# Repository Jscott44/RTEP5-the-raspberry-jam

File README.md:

<!-- display the social media buttons in your README -->

<!-- To Link your profile to the media buttons -->

# **The Raspberry Jam**

The realtime Raspberry PI powered digital guitar effects pedal.

<div style="float:left;margin:0 1px 1px 0" markdown="2">

</div>

# **Usage**

Ensure the Raspberry Pi is updated:

```bash
# Update package lists
sudo apt update

# Upgrade installed packages
sudo apt upgrade

# Remove unused packages
sudo apt autoremove

# Clean up package cache
sudo apt clean
```
Install Git 
```bash
# Install Git
sudo apt-get install git -y

# Verify Git installation
git --version
```
Install ALSA resources
```bash
# Install ALSA utilities and libraries
sudo apt-get install alsa-utils libasound2-dev -y

# Verify ALSA installation
aplay --version
```
Install CMake in order to build the project
```bash
# Install CMake
sudo apt-get install cmake -y

# Verify CMake installation
cmake --version
```
Clone the repository
```bash
# Clone the repository from GitHub
git clone https://github.com/Jscott44/RTEP5-the-raspberry-jam.git

# Change directory to the cloned repository
cd RTEP5-the-raspberry-jam

# List files in the repository
ls
```
For use with a generic sound card a device tree overlay needs to be created.

To make sound card master and Raspberry Pi on I2S bus (credit: https://github.com/AkiyukiOkayasu/RaspberryPi_I2S_Slave):
```bash
# Change to device tree directory
cd deviceTree

# Compile on Raspberry Pi  
dtc -@ -H epapr -O dtb -o genericstereoaudiocodec.dtbo -Wno-unit_address_vs_reg genericstereoaudiocodec.dts

# Copy i2smaster.dtbo to /boot/overlays  
sudo cp genericstereoaudiocodec.dtbo /boot/overlays

# Return to repository directory
cd ..
```

Edit /boot/config.txt   
```/boot/config.txt    # Uncomment some or all of these to enable the optional hardware interface
#dtparam=i2c_arm=on
dtparam=i2s=on
#dtparam=spi=on
dtoverlay=genericstereoaudiocodec
```
To make sound card slave and Raspberry Pi master on I2S bus (credit: https://github.com/AkiyukiOkayasu/RaspberryPi_I2S_Master):

```bash
# Compile on Raspberry Pi
# Change to device tree directory
cd deviceTree

dtc -@ -H epapr -O dtb -o i2smaster.dtbo -Wno-unit_address_vs_reg i2smaster.dts

# Copy i2smaster.dtbo to /boot/overlays  
sudo cp i2smaster.dtbo /boot/overlays

# Return to repository directory
cd ..
```

Edit /boot/config.txt  
```/boot/config.txt
# Uncomment some or all of these to enable the optional hardware interface
#dtparam=i2c_arm=on
dtparam=i2s=on
#dtparam=spi=on
dtoverlay=i2smaster
```

Bulding the project with CMake
```bash 
# Create a build directory (optional)
mkdir -p build
cd build

# Configure the build using CMake
cmake ..

# Build the project
make
```
# **Key Features**
- Realtime audio loop
- Cutsomisable effects
- User profiles
- Low cost
- Simple effect creation
- Specialised audio electronics design

# **Social Media Links**
[)][2]
[)][5]

[2]: https://www.instagram.com/the_raspberry_jam/ 
[5]: https://github.com/Jscott44/RTEP5-the-raspberry-jam

# **Authors and Roles**
- **Jed Scott**
  - Project Manager, Software (audio driver), Hardware Lead, Social Media Lead
- **Dario Petinella**
  - Software Lead (audio driver, effects manager), Integration Lead, Hardware (audio)
- **Alan Hamilton**
  - Software (GUI Lead and effects integration), Mechanical Support
- **Elad Perets**
  - Software (effects), Hardware (pedal)
- **Matthew Stewart**
  - Software (GUI)

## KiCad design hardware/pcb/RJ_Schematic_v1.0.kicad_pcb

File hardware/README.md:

# **Hardware**
The Raspberry Jam includes a specialised audio sound card for the capture and playback of high fidelity audio. The impact of the hardware is designed to be as inaudible as possible and all of the effects are achieved digitally in software. The hardware design is modular in nature allowing the cutsomisation to suit different applications.

# **Features**
- Highly integrated stereo audio CODEC
- Sample rates: 44.1kHz, 48kHz, 96kHz or 192kHz
- Hardware or Software control
- On-board oscillator
- 1x mono audio input (guitar)
- 2x stereo outputs (speakers)
- 1x stereo output (headphones with volume control)

# **Audio Inputs and Outputs**
The current version of the sound card supports one single ended mono instrument input up to 2Vrms. 

The output support two single ended connectors to create a stereo speaker output with a maximum level of 1.8Vrms before amplification. 

The output also support a headphone driver with analogue volume to control to adjust to different load impedance headphones.
- Default gain range 18dB.
- To alter gain range adjust R43, R44, R45 and R46.
- Adjust output power by altering R41 and R42.

# **CODEC**

<h2>CS4271 Sample Rate Truth Table</h2>

<table>
  <tr>
    <th>Resistor R49</th>
    <th>Resistor R50</th>
    <th>Resistor R10</th>
    <th>Resistor R11</th>
    <th>M1</th>
    <th>M0</th>
    <th>Sample Rate (kHz)</th>
  </tr>
  <tr>
    <td>Not Populated</td>
    <td>Not Populated</td>
    <td>Populated</td>
    <td>Populated</td>
    <td>0</td>
    <td>0</td>
    <td>44.1</td>
  </tr>
  <tr>
    <td>Not Populated</td>
    <td>Populated</td>
    <td>Populated</td>
    <td>Not Populated</td>
    <td>0</td>
    <td>1</td>
    <td>48</td>
  </tr>
  <tr>
    <td>Populated</td>
    <td>Not Populated</td>
    <td>Not Populated</td>
    <td>Populated</td>
    <td>1</td>
    <td>0</td>
    <td>96</td>
  </tr>
  <tr>
    <td>Populated</td>
    <td>Populated</td>
    <td>Not Populated</td>
    <td>Not Populated</td>
    <td>1</td>
    <td>1</td>
    <td>192</td>
  </tr>
</table>

</body>
</html>
</html>

<h2>CS4271 Audio Mode Truth Table</h2>

<table>
  <tr>
    <th>R9 </th>
    <th>R32 </th>
    <th>ADO </th>
    <th>Audio Mode</th>
  </tr>
  <tr>
    <td>Populated</td>
    <td>Not Populated</td>
    <td>1</td>
    <td>I2S</td>
  </tr>
  <tr>
    <td>Not Populated</td>
    <td>Populated</td>
    <td>0</td>
    <td>Left Justified</td>
  </tr>

  </tr>
</table>

</body>
</html>

# **Digital Audio Format**

By default the digital audio interface will operate using the I2S protocol
- MSB first (big endian)
- Signed 24-bits per channel
- 2 channels
- Interleaved channels

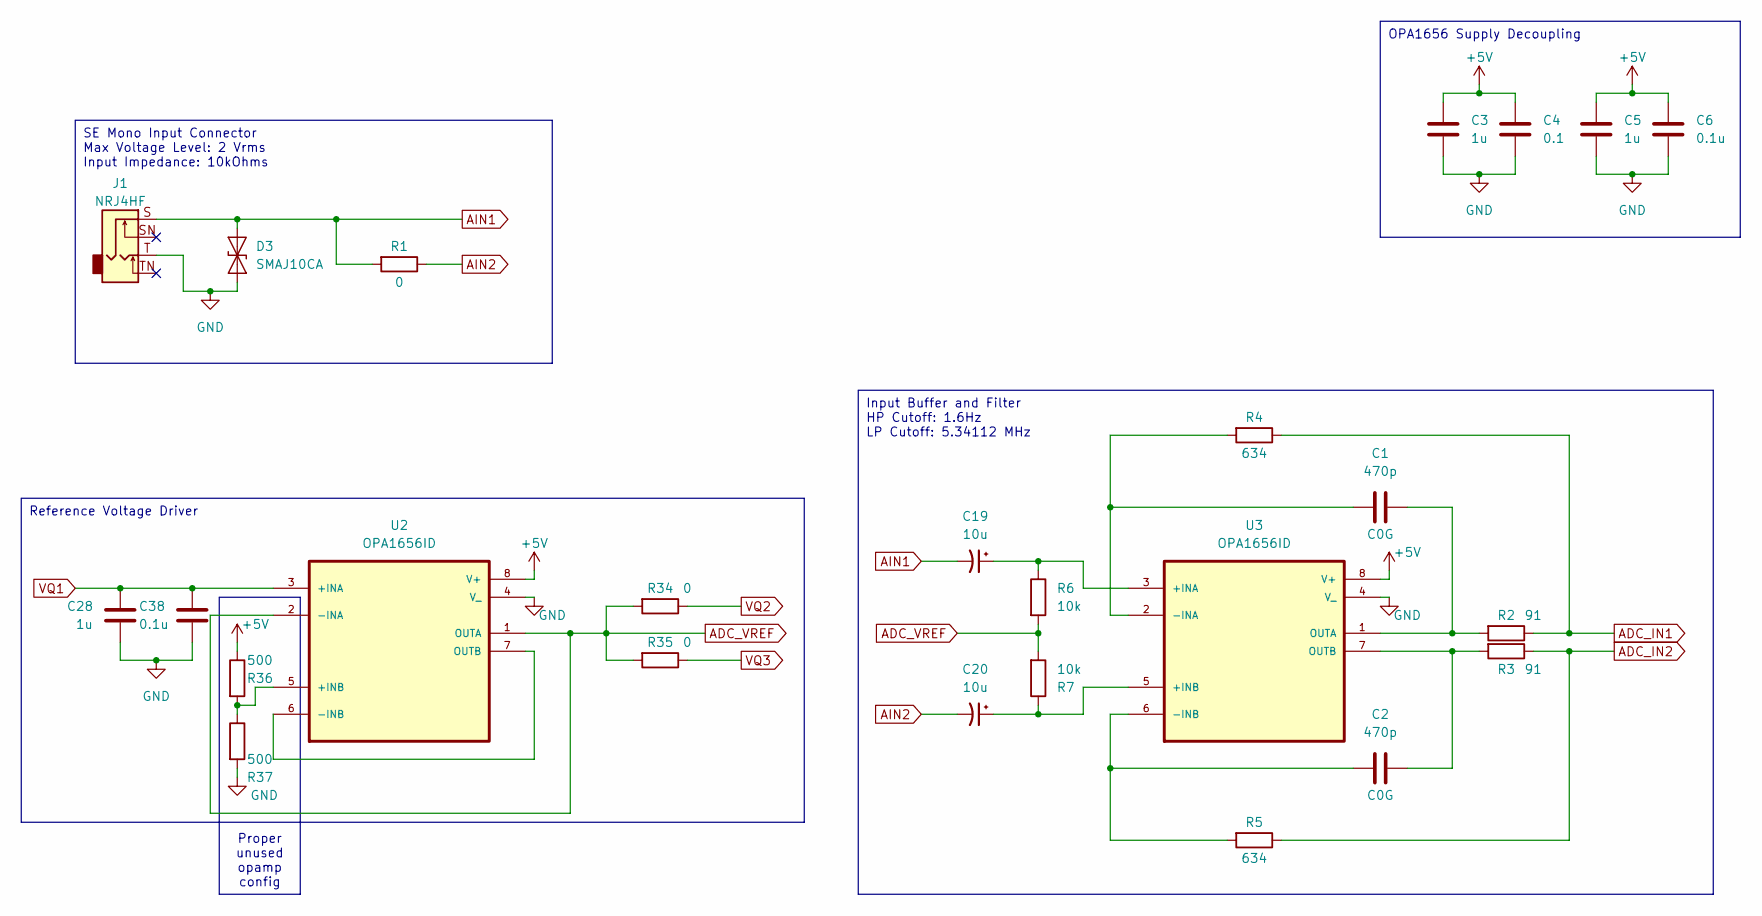
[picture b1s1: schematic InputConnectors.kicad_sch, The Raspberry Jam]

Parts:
C1, C2: 470p; C_0805_2012Metric_Pad1.18x1.45mm_HandSolder
C3, C5, C28: 1u; C_0805_2012Metric_Pad1.18x1.45mm_HandSolder
C4: 0.1; C_0805_2012Metric_Pad1.18x1.45mm_HandSolder
C6, C38: 0.1u; C_0805_2012Metric_Pad1.18x1.45mm_HandSolder
C19, C20: 10u; CP_Elec_4x5.4
D3: SMAJ10CA; D_SMA
J1: NRJ4HF; Jack_6.35mm_Neutrik_NRJ4HF_Horizontal
R1, R34, R35: 0; R_0805_2012Metric_Pad1.20x1.40mm_HandSolder
R2, R3: 91; R_0805_2012Metric_Pad1.20x1.40mm_HandSolder
R4, R5: 634; R_0805_2012Metric_Pad1.20x1.40mm_HandSolder
R6, R7: 10k; R_0805_2012Metric_Pad1.20x1.40mm_HandSolder
R36, R37: 500; R_0805_2012Metric_Pad1.20x1.40mm_HandSolder
U2, U3: OPA1656ID; SOIC127P599X175-8N

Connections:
+5V: C3.2, C4.2, C5.2, C6.2, R36.1, U2.8 (V+), U3.8 (V+); also elsewhere on the board
ADC_IN1: R2.1, R4.1; also elsewhere on the board
ADC_IN2: R3.1, R5.1; also elsewhere on the board
ADC_VREF: R6.2, R7.2, R34.2, R35.2, U2.1 (OUTA), U2.2 (-INA)
AIN1: C19.2, D3.2 (A2), J1.S, R1.2
AIN2: C20.2, R1.1
GND: C3.1, C4.1, C5.1, C6.1, C28.1, C38.1, D3.1 (A1), J1.T, R37.2, U2.4 (V_), U3.4 (V_); also elsewhere on the board
unnamed: R36.2, R37.1, U2.5 (+INB)
unnamed: U2.6 (-INB), U2.7 (OUTB)
unnamed: C19.1, R6.1, U3.3 (+INA)
unnamed: C20.1, R7.1, U3.5 (+INB)
unnamed: C1.2, R4.2, U3.2 (-INA)
unnamed: C2.2, R5.2, U3.6 (-INB)
unnamed: C1.1, R2.2, U3.1 (OUTA)
unnamed: C2.1, R3.2, U3.7 (OUTB)
VQ1: C28.2, C38.2, U2.3 (+INA); also elsewhere on the board
VQ2: R34.1; also elsewhere on the board
VQ3: R35.1; also elsewhere on the board

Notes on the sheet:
Proper unused opamp config
Input Buffer and Filter HP Cutoff: 1.6Hz LP Cutoff: 5.34112 MHz
OPA1656 Supply Decoupling
Reference Voltage Driver
SE Mono Input Connector Max Voltage Level: 2 Vrms Input Impedance: 10kOhms

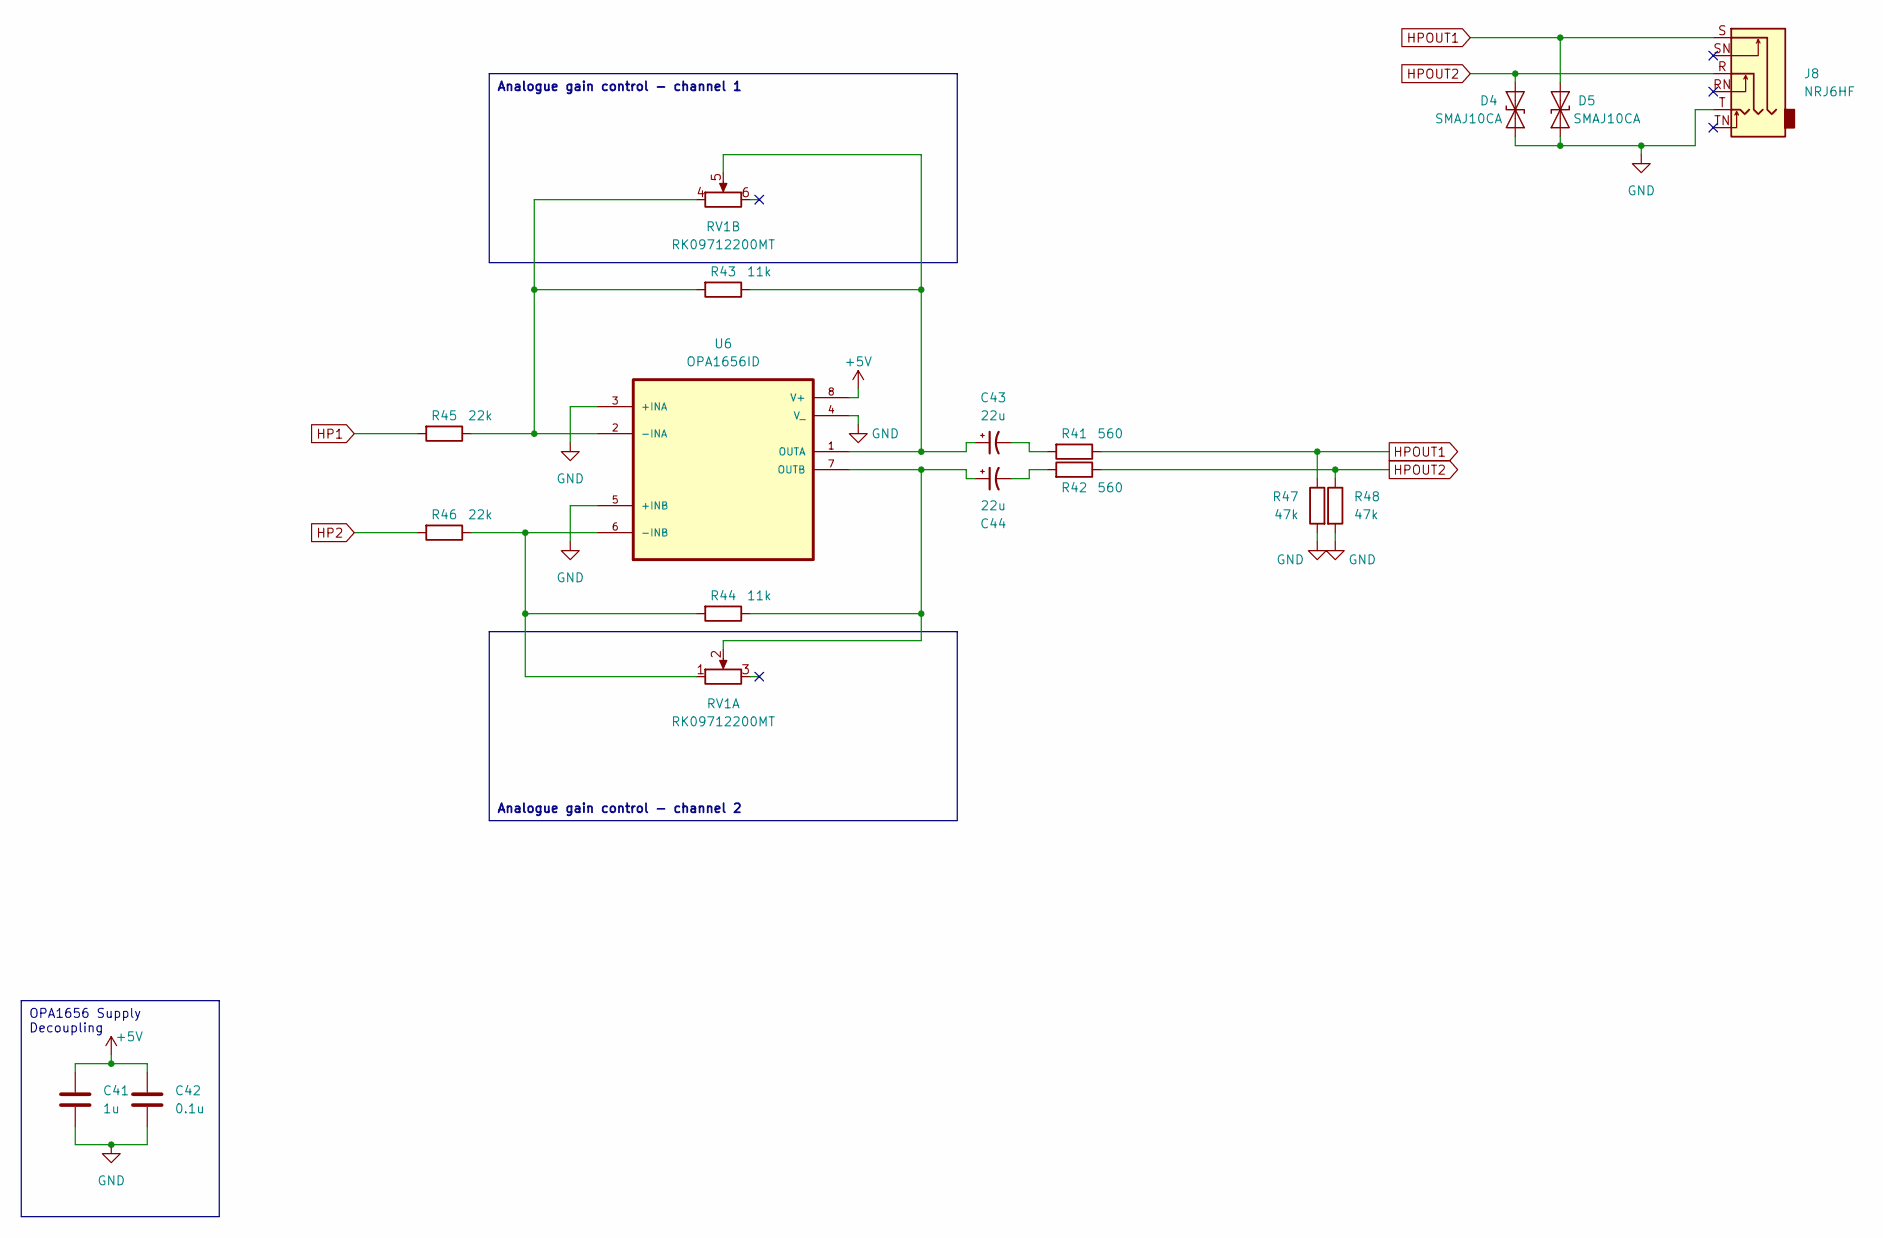
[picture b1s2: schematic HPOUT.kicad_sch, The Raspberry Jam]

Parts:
C41: 1u; C_0805_2012Metric_Pad1.18x1.45mm_HandSolder
C42: 0.1u; C_0805_2012Metric_Pad1.18x1.45mm_HandSolder
C43, C44: 22u; CP_Elec_5x5.7
D4, D5: SMAJ10CA; D_SMA
J8: NRJ6HF; Jack_6.35mm_Neutrik_NRJ6HF_Horizontal
R41, R42: 560; R_0805_2012Metric_Pad1.20x1.40mm_HandSolder
R43, R44: 11k; R_0805_2012Metric_Pad1.20x1.40mm_HandSolder
R45, R46: 22k; R_0805_2012Metric_Pad1.20x1.40mm_HandSolder
R47, R48: 47k; R_0805_2012Metric_Pad1.20x1.40mm_HandSolder
RV1: RK09712200MT; Potentiometer_Alps_RK097_Dual_Horizontal
U6: OPA1656ID; SOIC127P599X175-8N

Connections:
+5V: C41.2, C42.2, U6.8 (V+); also elsewhere on the board
GND: C41.1, C42.1, D4.1 (A1), D5.1 (A1), J8.T, R47.2, R48.2, U6.3 (+INA), U6.4 (V_), U6.5 (+INB); also elsewhere on the board
HP1: R45.2; also elsewhere on the board
HP2: R46.2; also elsewhere on the board
HPOUT1: D5.2 (A2), J8.S, R41.1, R47.1
HPOUT2: D4.2 (A2), J8.R, R42.1, R48.1
unnamed: C43.2, R41.2
unnamed: C44.2, R42.2
unnamed: R43.2, R45.1, RV1.4, U6.2 (-INA)
unnamed: R44.2, R46.1, RV1.1, U6.6 (-INB)
unnamed: C43.1, R43.1, RV1.5, U6.1 (OUTA)
unnamed: C44.1, R44.1, RV1.2, U6.7 (OUTB)

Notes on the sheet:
OPA1656 Supply Decoupling
Analogue gain control - channel 2
Analogue gain control - channel 1

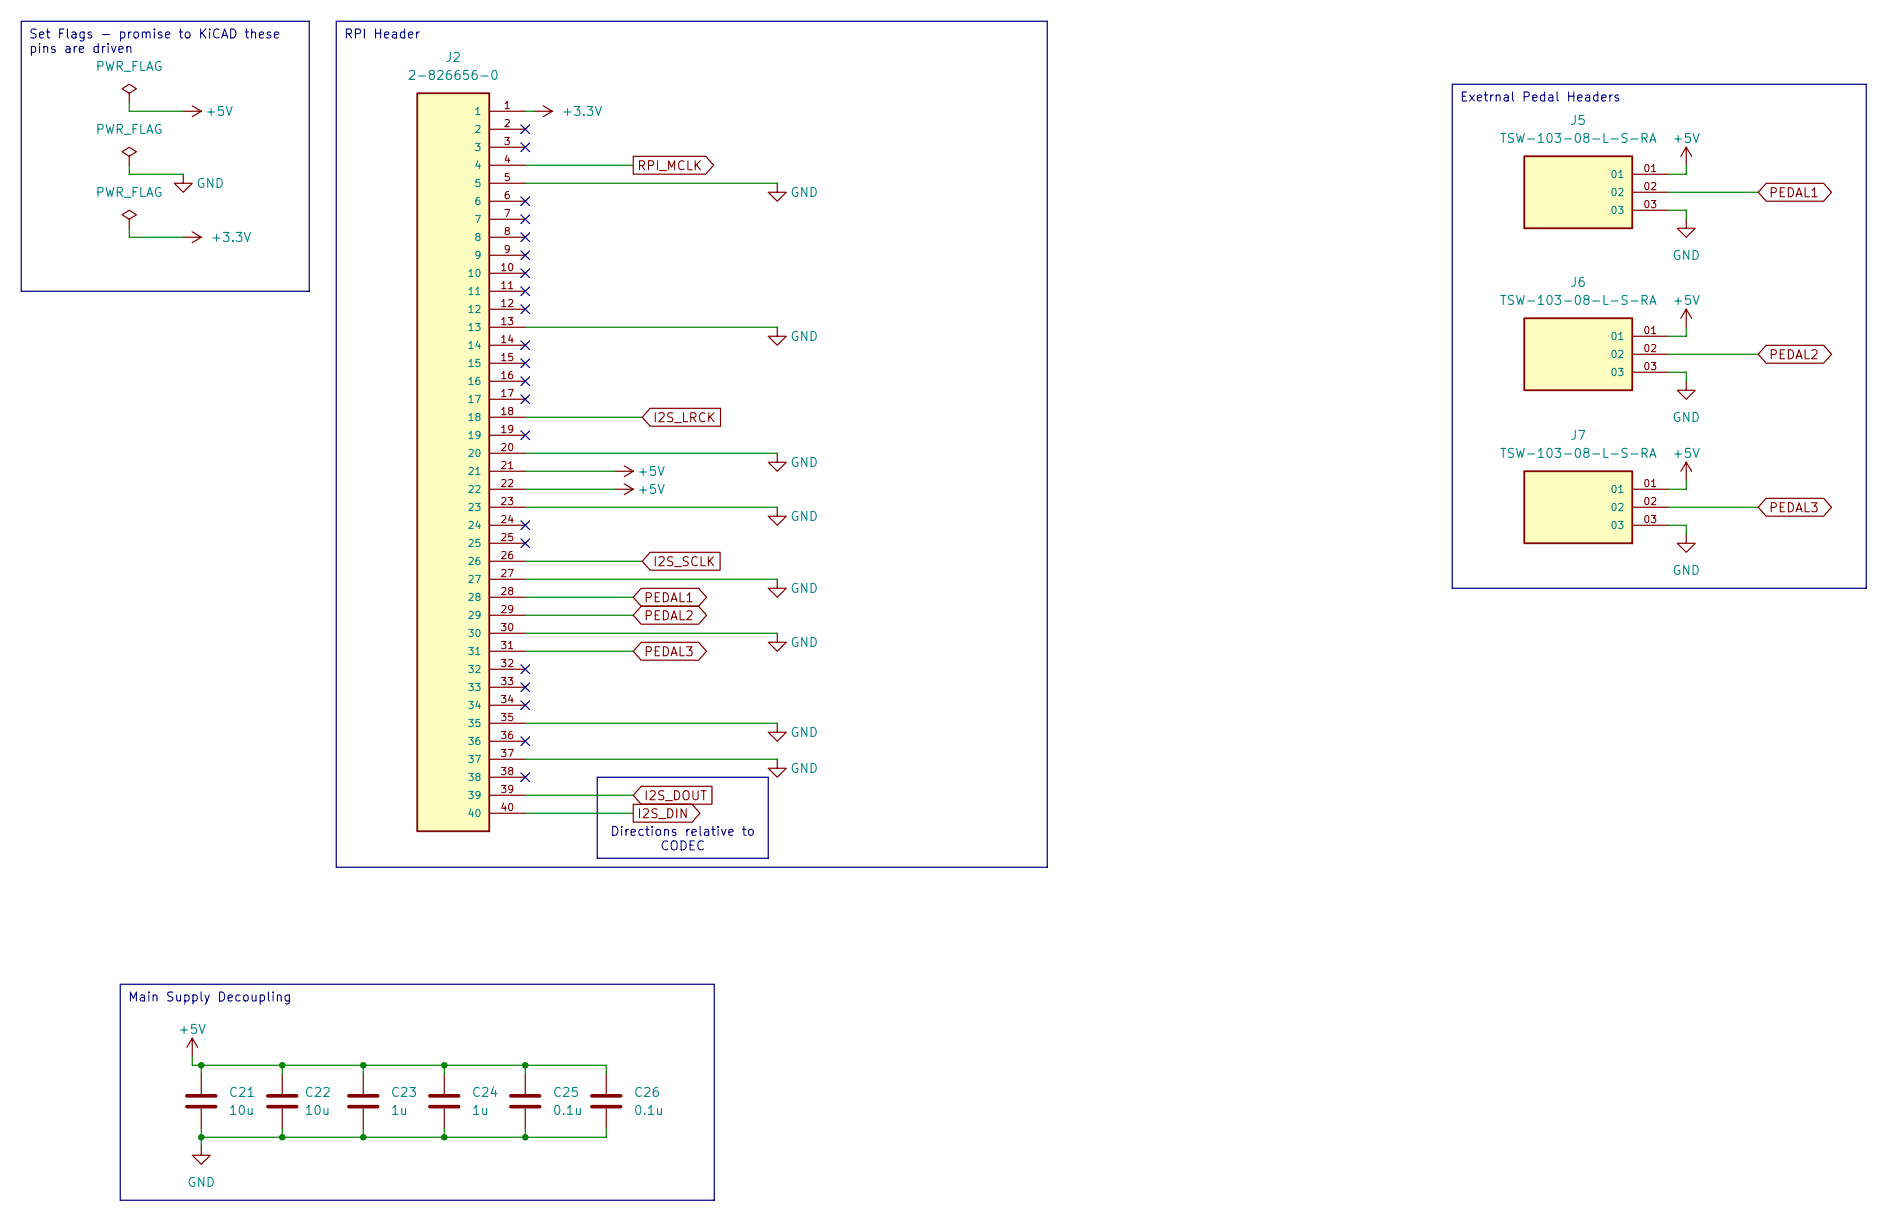
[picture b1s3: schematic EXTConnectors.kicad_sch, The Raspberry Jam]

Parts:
C21, C22: 10u; C_0805_2012Metric_Pad1.18x1.45mm_HandSolder
C23, C24: 1u; C_0805_2012Metric_Pad1.18x1.45mm_HandSolder
C25, C26: 0.1u; C_0805_2012Metric_Pad1.18x1.45mm_HandSolder
J2: 2-826656-0; TE_2-826656-0; PARTREV R
J5, J6, J7: TSW-103-08-L-S-RA; SAMTEC_TSW-103-08-L-S-RA; PARTREV R

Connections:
+3.3V: J2.1; also elsewhere on the board
+5V: C21.1, C22.1, C23.1, C24.1, C25.1, C26.1, J2.21, J2.22, J5.01, J6.01, J7.01; also elsewhere on the board
GND: C21.2, C22.2, C23.2, C24.2, C25.2, C26.2, J2.5, J2.13, J2.20, J2.23, J2.27, J2.30, J2.35, J2.37, J5.03, J6.03, J7.03; also elsewhere on the board
I2S_DIN: J2.40; also elsewhere on the board
I2S_DOUT: J2.39; also elsewhere on the board
I2S_LRCK: J2.18; also elsewhere on the board
I2S_SCLK: J2.26; also elsewhere on the board
PEDAL1: J2.28, J5.02
PEDAL2: J2.29, J6.02
PEDAL3: J2.31, J7.02
RPI_MCLK: J2.4; also elsewhere on the board

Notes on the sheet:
Exetrnal Pedal Headers
RPI Header
Directions relative to CODEC
Main Supply Decoupling
Set Flags - promise to KiCAD these pins are driven

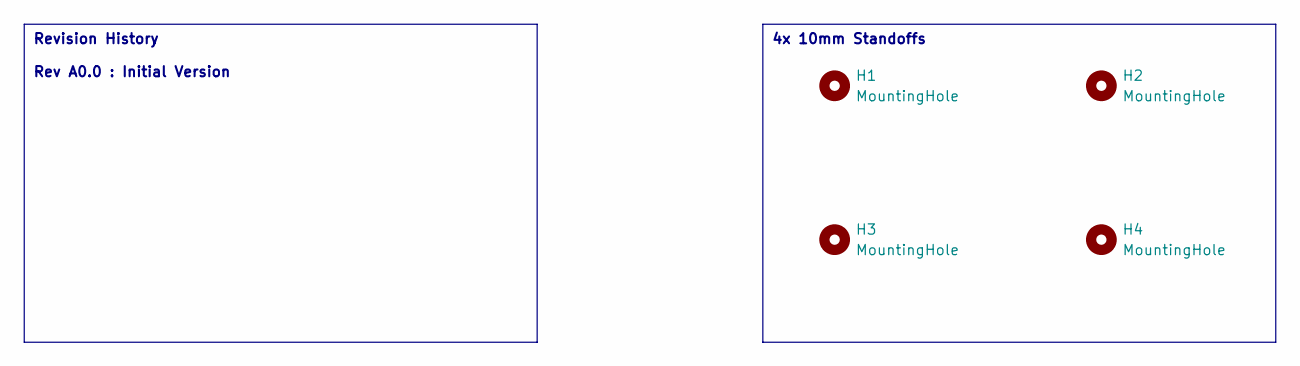
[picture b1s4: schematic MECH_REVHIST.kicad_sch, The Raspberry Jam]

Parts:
H1, H2, H3, H4: MountingHole; MountingHole_2.2mm_M2

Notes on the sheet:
Revision History Rev A0.0 : Initial Version
4x 10mm Standoffs

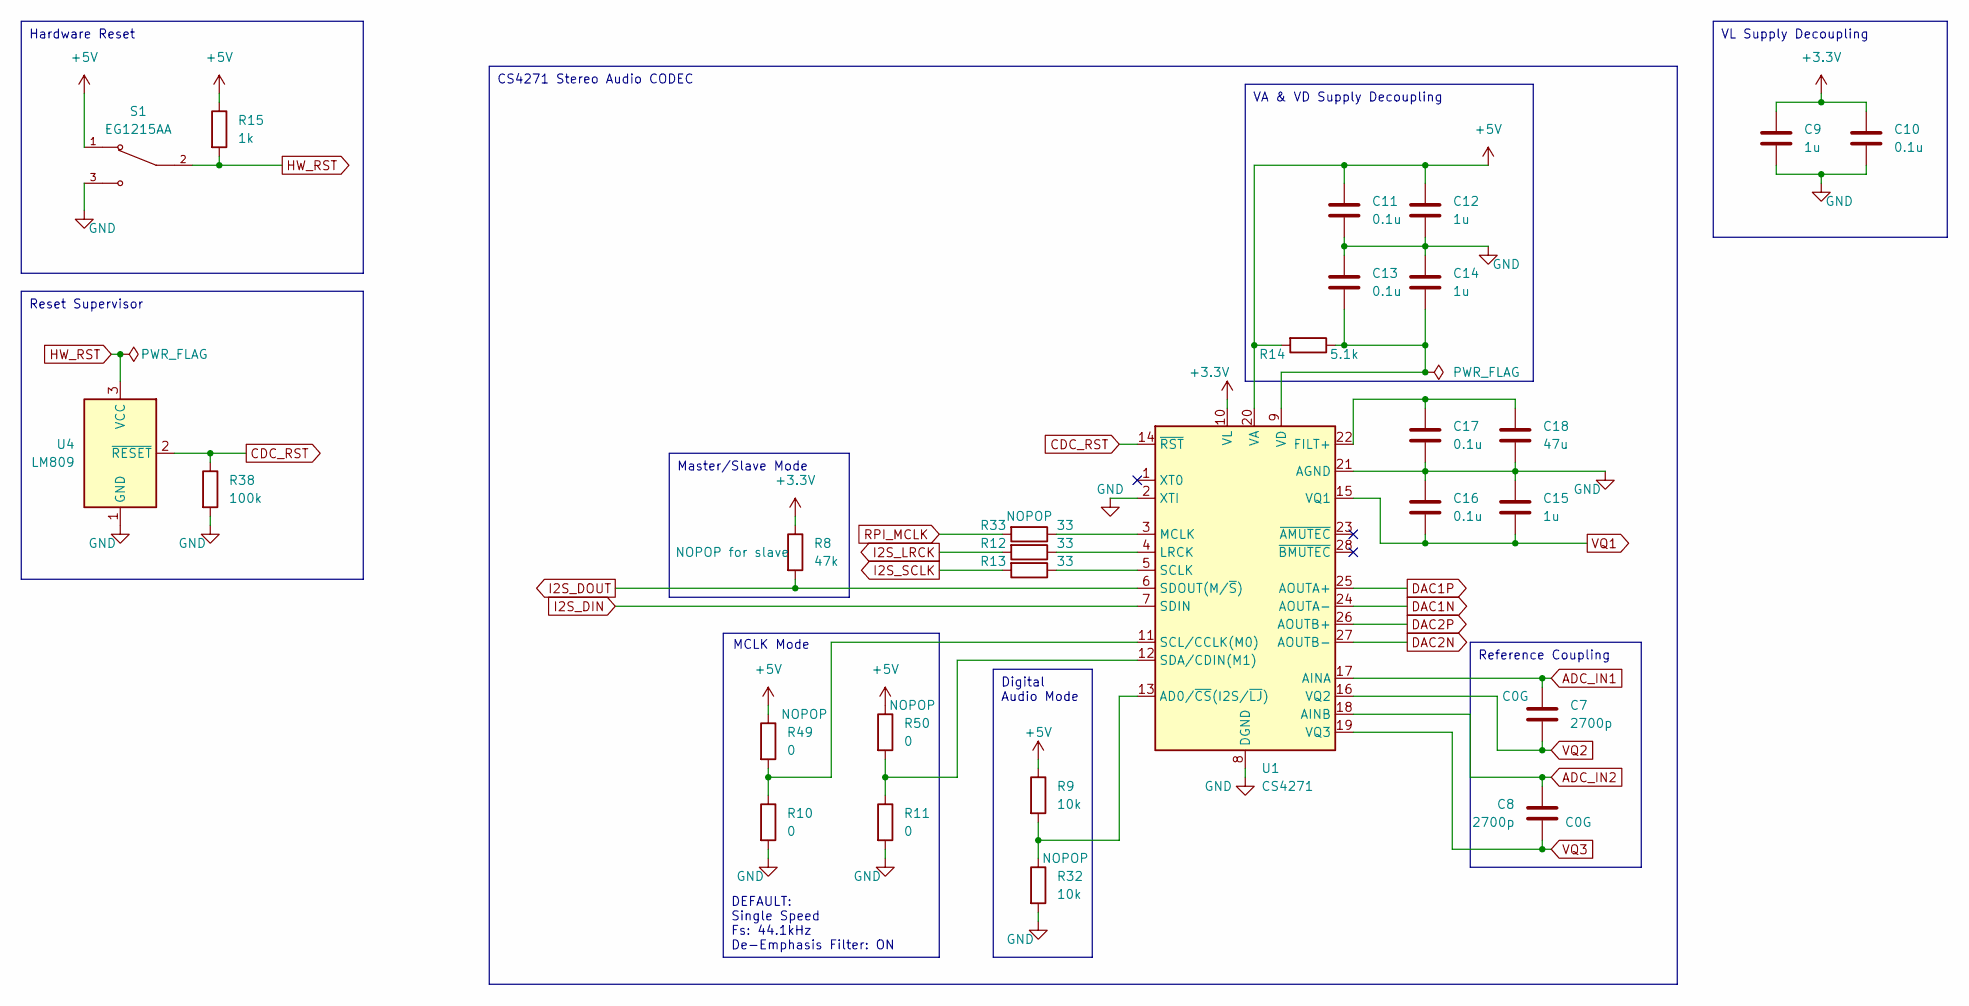
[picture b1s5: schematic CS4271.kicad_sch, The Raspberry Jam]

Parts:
C7, C8: 2700p; C_0805_2012Metric_Pad1.18x1.45mm_HandSolder
C9, C12, C14, C15: 1u; C_0805_2012Metric_Pad1.18x1.45mm_HandSolder
C10, C11, C13, C16, C17: 0.1u; C_0805_2012Metric_Pad1.18x1.45mm_HandSolder
C18: 47u; C_0805_2012Metric_Pad1.18x1.45mm_HandSolder
R8: 47k; R_0805_2012Metric_Pad1.20x1.40mm_HandSolder
R9, R32: 10k; R_0805_2012Metric_Pad1.20x1.40mm_HandSolder
R10, R11, R49, R50: 0; R_0805_2012Metric_Pad1.20x1.40mm_HandSolder
R12, R13, R33: 33; R_0805_2012Metric_Pad1.20x1.40mm_HandSolder
R14: 5.1k; R_0805_2012Metric_Pad1.20x1.40mm_HandSolder
R15: 1k; R_0805_2012Metric_Pad1.20x1.40mm_HandSolder
R38: 100k; R_0805_2012Metric_Pad1.20x1.40mm_HandSolder
S1: EG1215AA; SW_EG1215AA; PARTREV A
U1: CS4271; TSSOP-28_4.4x9.7mm_P0.65mm
U4: LM809; SOT-23

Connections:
+3.3V: C9.1, C10.1, R8.1, U1.10 (VL); also elsewhere on the board
+5V: C11.1, C12.1, R9.1, R14.2, R15.1, R49.1, R50.1, S1.1, U1.20 (VA); also elsewhere on the board
ADC_IN1: C7.1, U1.17 (AINA); also elsewhere on the board
ADC_IN2: C8.2, U1.18 (AINB); also elsewhere on the board
CDC_RST: R38.1, U1.14 (~RST), U4.2 (~RESET)
DAC1N: U1.24 (AOUTA-); also elsewhere on the board
DAC1P: U1.25 (AOUTA+); also elsewhere on the board
DAC2N: U1.27 (AOUTB-); also elsewhere on the board
DAC2P: U1.26 (AOUTB+); also elsewhere on the board
GND: C9.2, C10.2, C11.2, C12.2, C13.1, C14.1, C15.1, C16.1, C17.2, C18.2, R10.2, R11.2, R32.2, R38.2, S1.3, U1.2 (XTI), U1.8 (DGND), U1.21 (AGND), U4.1 (GND); also elsewhere on the board
HW_RST: R15.2, S1.2, U4.3 (VCC)
I2S_DIN: U1.7 (SDIN); also elsewhere on the board
I2S_DOUT: R8.2, U1.6 (SDOUT(M/~S)); also elsewhere on the board
I2S_LRCK: R12.2; also elsewhere on the board
I2S_SCLK: R13.2; also elsewhere on the board
unnamed: R9.2, R32.1, U1.13 (AD0/~CS(I2S/~LJ))
unnamed: C17.1, C18.1, U1.22 (FILT+)
unnamed: R12.1, U1.4 (LRCK)
unnamed: R33.1, U1.3 (MCLK)
unnamed: R13.1, U1.5 (SCLK)
unnamed: R10.1, R49.2, U1.11 (SCL/CCLK(M0))
unnamed: R11.1, R50.2, U1.12 (SDA/CDIN(M1))
unnamed: C13.2, C14.2, R14.1, U1.9 (VD)
RPI_MCLK: R33.2; also elsewhere on the board
VQ1: C15.2, C16.2, U1.15 (VQ1); also elsewhere on the board
VQ2: C7.2, U1.16 (VQ2); also elsewhere on the board
VQ3: C8.1, U1.19 (VQ3); also elsewhere on the board

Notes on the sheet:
DEFAULT: Single Speed Fs: 44.1kHz De-Emphasis Filter: ON
Hardware Reset
Digital Audio Mode
Reset Supervisor
Reference Coupling
Master/Slave Mode
CS4271 Stereo Audio CODEC
VL Supply Decoupling
VA & VD Supply Decoupling
MCLK Mode

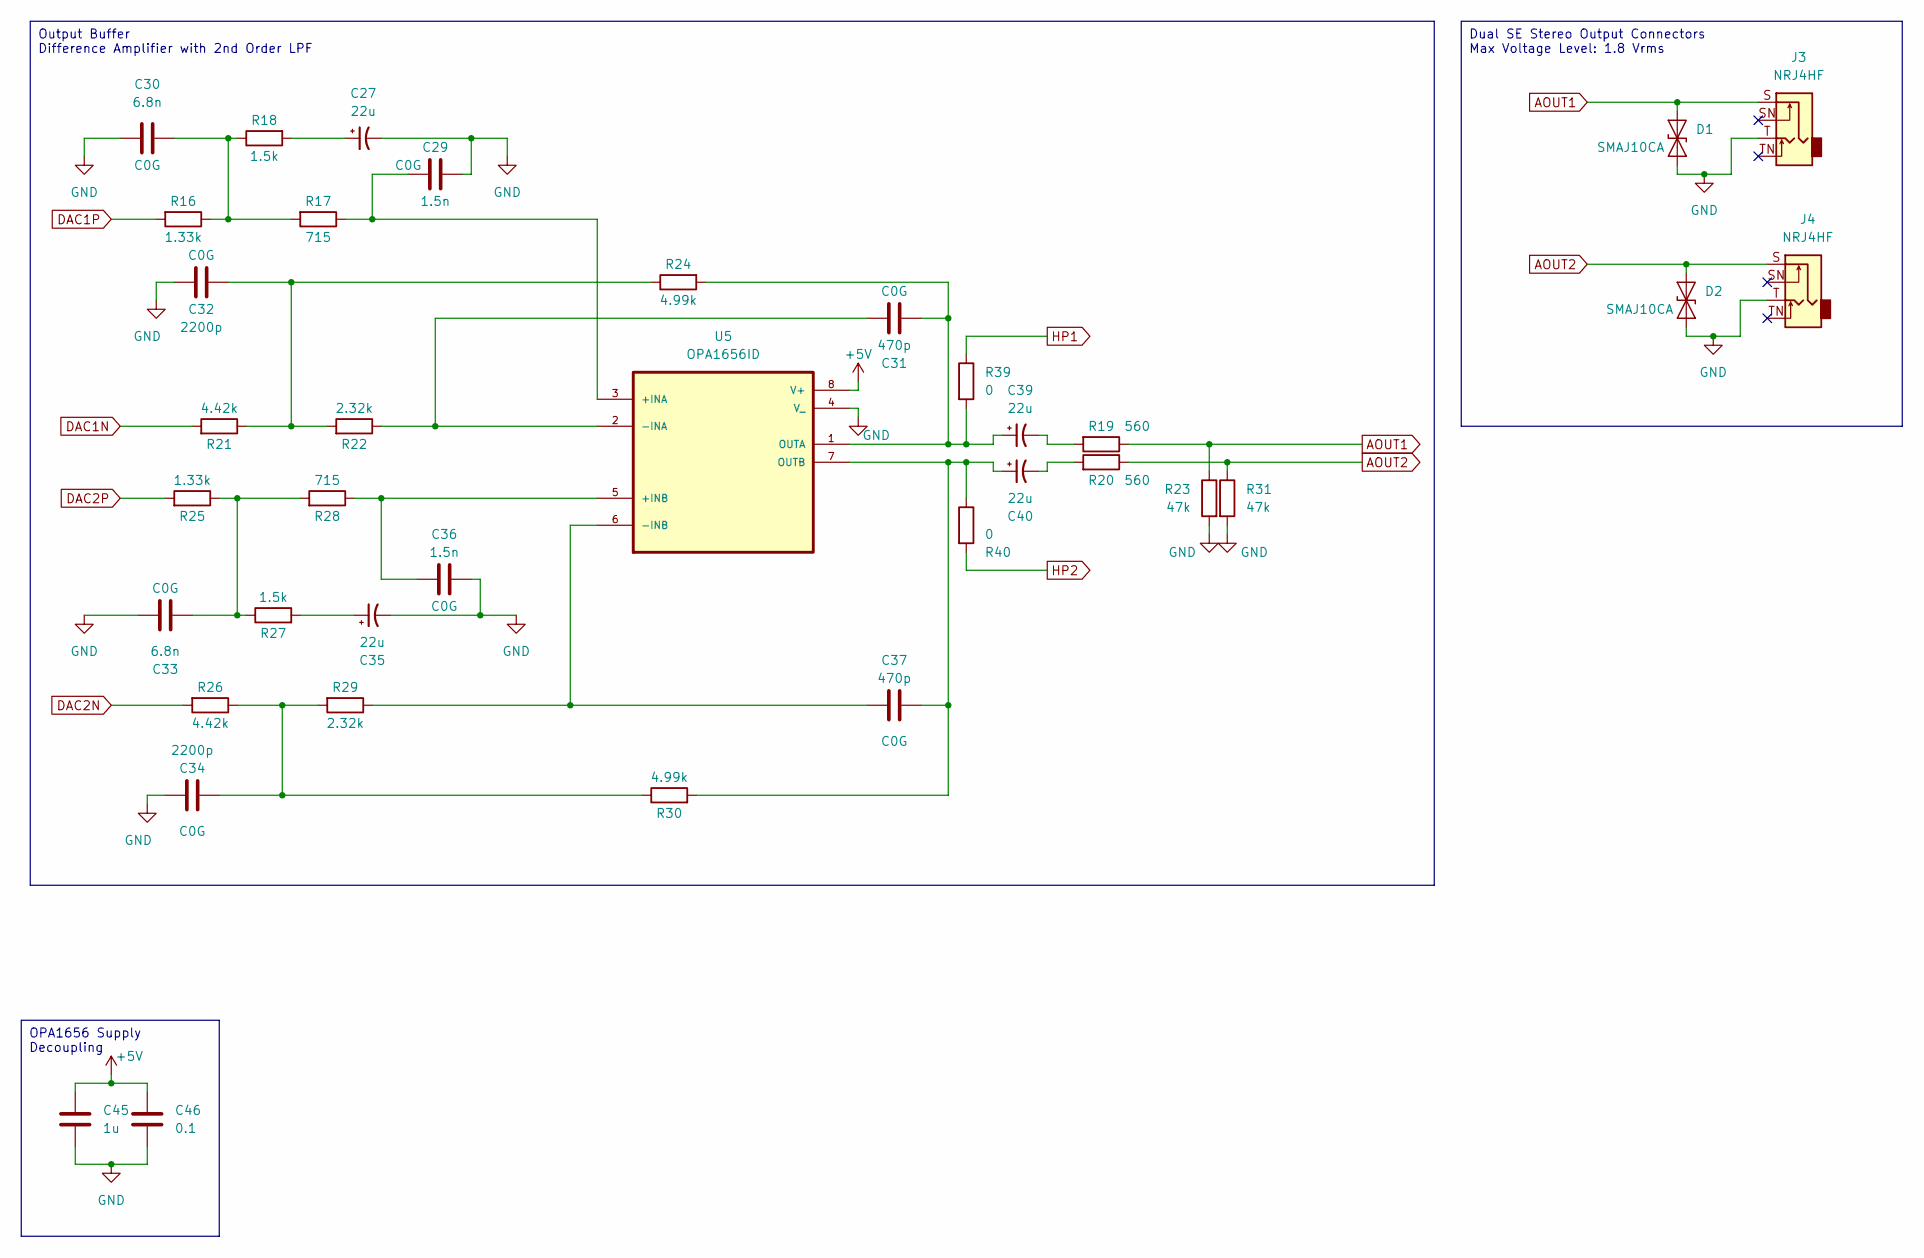
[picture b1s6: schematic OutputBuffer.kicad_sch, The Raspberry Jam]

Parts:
C27, C35, C39, C40: 22u; CP_Elec_5x5.7
C29, C36: 1.5n; C_0805_2012Metric_Pad1.18x1.45mm_HandSolder
C30, C33: 6.8n; C_0805_2012Metric_Pad1.18x1.45mm_HandSolder
C31, C37: 470p; C_0805_2012Metric_Pad1.18x1.45mm_HandSolder
C32, C34: 2200p; C_0805_2012Metric_Pad1.18x1.45mm_HandSolder
C45: 1u; C_0805_2012Metric_Pad1.18x1.45mm_HandSolder
C46: 0.1; C_0805_2012Metric_Pad1.18x1.45mm_HandSolder
D1, D2: SMAJ10CA; D_SMA
J3, J4: NRJ4HF; Jack_6.35mm_Neutrik_NRJ4HF_Horizontal
R16, R25: 1.33k; R_0805_2012Metric_Pad1.20x1.40mm_HandSolder
R17, R28: 715; R_0805_2012Metric_Pad1.20x1.40mm_HandSolder
R18, R27: 1.5k; R_0805_2012Metric_Pad1.20x1.40mm_HandSolder
R19, R20: 560; R_0805_2012Metric_Pad1.20x1.40mm_HandSolder
R21, R26: 4.42k; R_0805_2012Metric_Pad1.20x1.40mm_HandSolder
R22, R29: 2.32k; R_0805_2012Metric_Pad1.20x1.40mm_HandSolder
R23, R31: 47k; R_0805_2012Metric_Pad1.20x1.40mm_HandSolder
R24, R30: 4.99k; R_0805_2012Metric_Pad1.20x1.40mm_HandSolder
R39, R40: 0; R_0805_2012Metric_Pad1.20x1.40mm_HandSolder
U5: OPA1656ID; SOIC127P599X175-8N

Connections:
+5V: C45.2, C46.2, U5.8 (V+); also elsewhere on the board
AOUT1: D1.2 (A2), J3.S, R19.1, R23.1
AOUT2: D2.2 (A2), J4.S, R20.1, R31.1
DAC1N: R21.2; also elsewhere on the board
DAC1P: R16.2; also elsewhere on the board
DAC2N: R26.2; also elsewhere on the board
DAC2P: R25.2; also elsewhere on the board
GND: C27.2, C29.2, C30.1, C32.1, C33.1, C34.1, C35.2, C36.2, C45.1, C46.1, D1.1 (A1), D2.1 (A1), J3.T, J4.T, R23.2, R31.2, U5.4 (V_); also elsewhere on the board
HP1: R39.1; also elsewhere on the board
HP2: R40.2; also elsewhere on the board
unnamed: C27.1, R18.2
unnamed: C30.2, R16.1, R17.2, R18.1
unnamed: C32.2, R21.1, R22.2, R24.1
unnamed: C33.2, R25.1, R27.1, R28.2
unnamed: C34.2, R26.1, R29.2, R30.1
unnamed: C35.1, R27.2
unnamed: C39.2, R19.2
unnamed: C40.2, R20.2
unnamed: C29.1, R17.1, U5.3 (+INA)
unnamed: C36.1, R28.1, U5.5 (+INB)
unnamed: C31.1, R22.1, U5.2 (-INA)
unnamed: C37.1, R29.1, U5.6 (-INB)
unnamed: C31.2, C39.1, R24.2, R39.2, U5.1 (OUTA)
unnamed: C37.2, C40.1, R30.2, R40.1, U5.7 (OUTB)

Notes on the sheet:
Output Buffer Difference Amplifier with 2nd Order LPF
OPA1656 Supply Decoupling
Dual SE Stereo Output Connectors Max Voltage Level: 1.8 Vrms

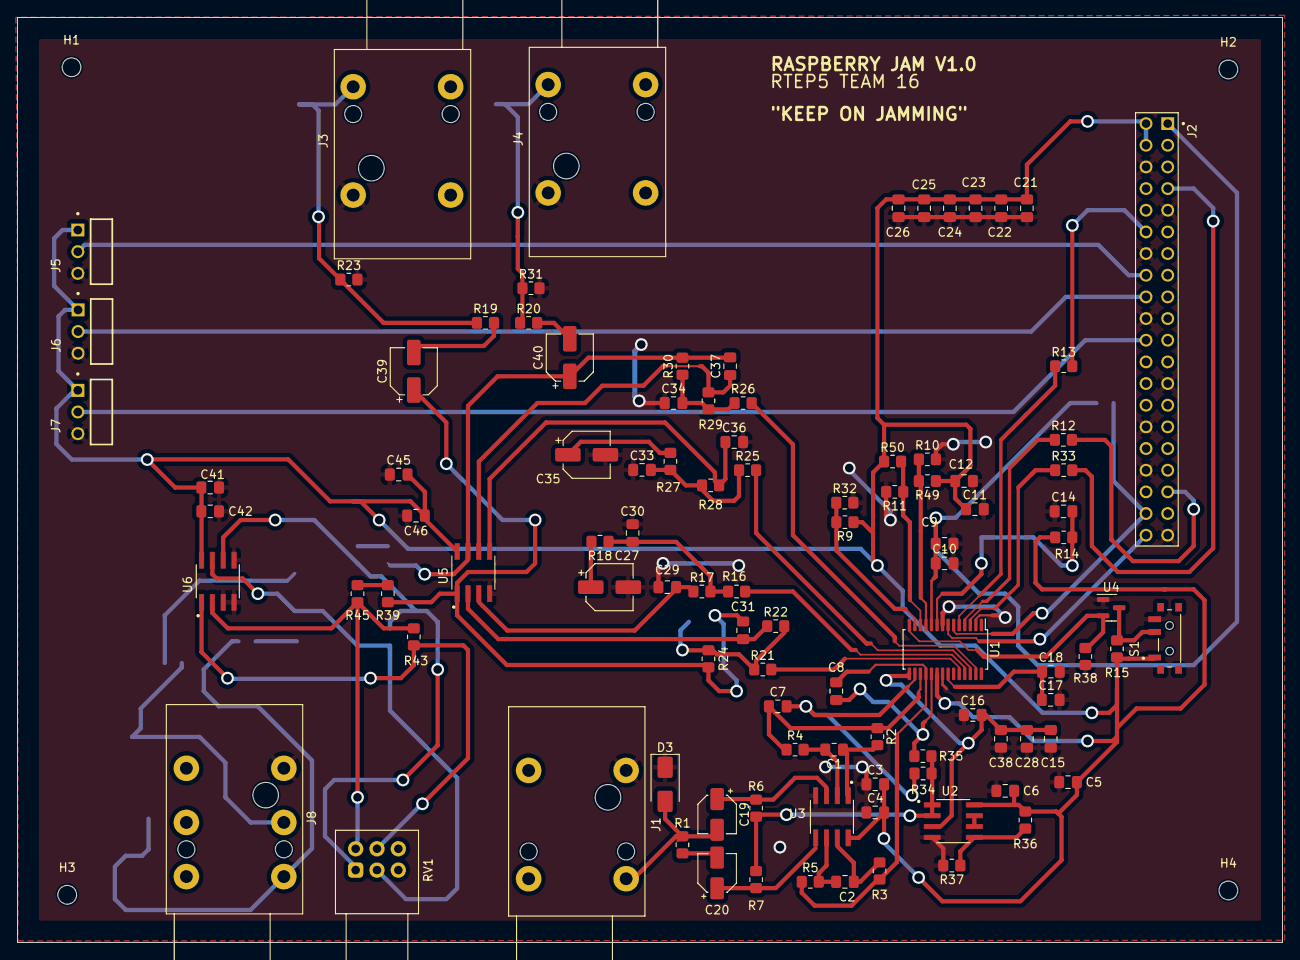
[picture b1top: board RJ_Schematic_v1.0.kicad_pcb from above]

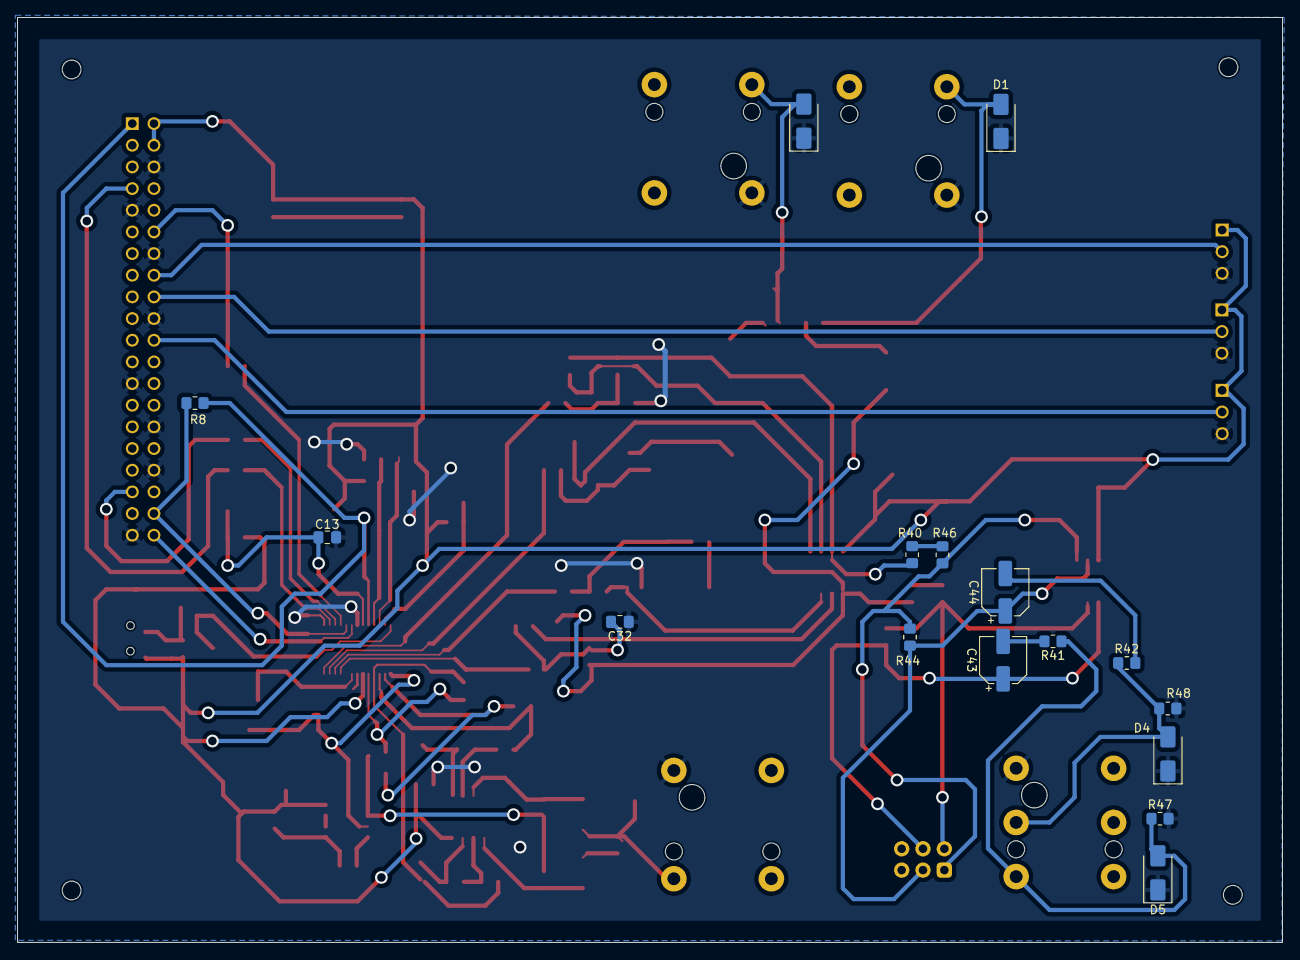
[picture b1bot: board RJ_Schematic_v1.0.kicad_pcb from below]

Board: 2 copper layers, 148.3 x 108.4 mm, 121 parts (16 on the bottom side), 67 nets.
